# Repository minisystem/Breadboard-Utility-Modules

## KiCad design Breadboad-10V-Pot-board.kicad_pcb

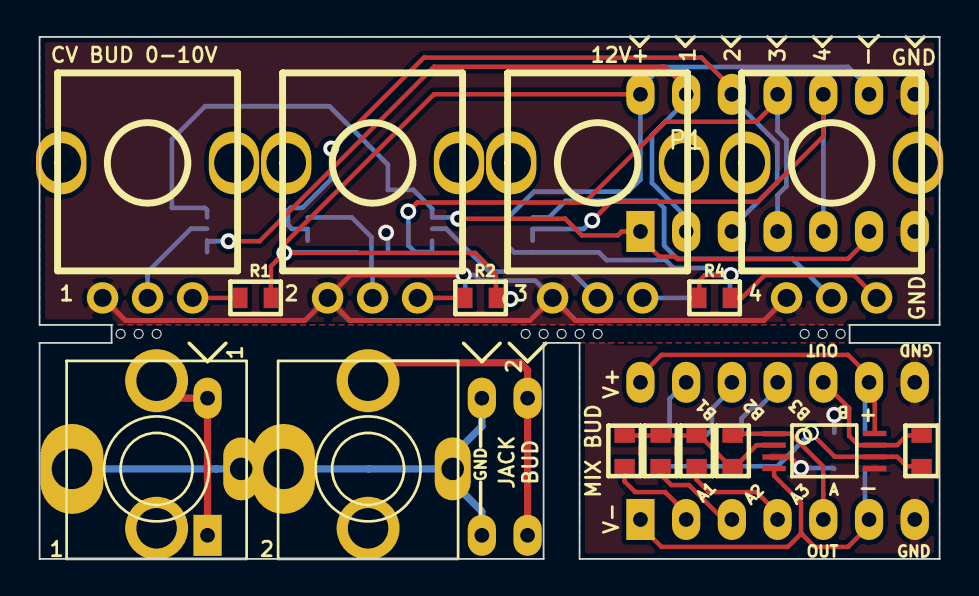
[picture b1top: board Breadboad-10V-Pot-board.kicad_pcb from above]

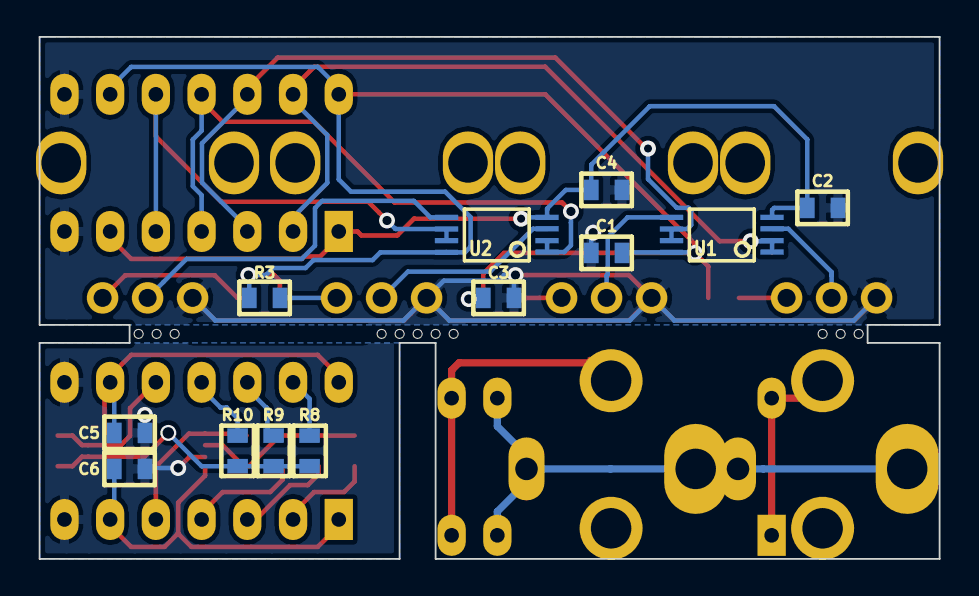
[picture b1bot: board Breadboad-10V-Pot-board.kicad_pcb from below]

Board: 2 copper layers, 50.0 x 29.0 mm, 44 parts (12 on the bottom side), 27 nets.

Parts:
C1, C2, C3, C4, C5, C6: C_US; SM0603-C-JRL
HOLE-0.125-INCH, HOLE-0.125-INCH#2, HOLE-0.125-INCH#3, HOLE-0.125-INCH#4, HOLE-0.125-INCH#5, HOLE-0.125-INCH#6, HOLE-0.125-INCH#7, HOLE-0.125-INCH#8, HOLE-0.125-INCH#9, HOLE-0.125-INCH#10, HOLE-0.125-INCH#11, HOLE-0.125-INCH#12, HOLE-0.125-INCH#13: VAL**; HOLE-0.125-INCH
J1, J2: JACK_MONO_SW; PJ-301B-JACK
P1, P2: DIP14; DIP-14__300_ELL
P3, P3#2: DIP_6; DIP-6__300_ELL
R1, R2, R3, R4: 10K; SM0603-R-JRL
R5, R6, R7, R8, R9, R10, R11, R12: 100K; SM0603-R-JRL
U1, U2, U3: TL072-; TSSOP8-JRL
VR1, VR2, VR3, VR4: 50K; RD901F-ALPHA-POT

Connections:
+12V: C1.1, C3.1, C5.1, P1.9, P1.14, P2.9, P2.14, R1.1, R2.1, R3.1, R4.1, U1.8, U2.8, U3.8
-12V: C2.2, C4.2, C6.2, P1.1, P1.6, P2.1, P2.6, U1.4, U2.4, U3.4
CV1: P1.2, P1.13, U1.1, U1.2
CV2: P1.3, P1.12, U1.6, U1.7
CV3: P1.4, P1.11, U2.1, U2.2
CV4: P1.5, P1.10, U2.6, U2.7
GND: C1.2, C2.1, C3.2, C4.1, C5.2, C6.1, J1.1, J2.1, P1.7, P1.8, P2.7, P2.8, P3#2.2, P3#2.5, U3.3, U3.5, VR1.1, VR2.1, VR3.1, VR4.1
JACK1: J1.3, P3.1, P3.6
JACK2: J2.3, P3#2.3, P3#2.4
MIXA-IN1: P2.2, R5.2
MIXA-IN2: P2.3, R6.2
MIXA-IN3: P2.4, R7.2
MIXA-OUT: P2.5, R11.1, U3.1
MIXB-IN1: P2.13, R8.2
MIXB-IN2: P2.12, R9.2
MIXB-IN3: P2.11, R10.2
MIXB-OUT: P2.10, R12.1, U3.7
unnamed: R1.2, VR1.3
unnamed: R2.2, VR2.3
unnamed: R3.2, VR3.3
unnamed: R4.2, VR4.3
unnamed: R8.1, R9.1, R10.1, R12.2, U3.6
unnamed: R5.1, R6.1, R7.1, R11.2, U3.2
unnamed: U1.3, VR1.2
unnamed: U1.5, VR2.2
unnamed: U2.3, VR3.2
unnamed: U2.5, VR4.2

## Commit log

2015-04-11 added jack board and laid out mechanical holes for panel separation
2015-04-11 cleaning up silkscreen
2015-04-12 silkscreen adjusted, ready to order. May have problem with NPTH holes with DirtyPCBs
2015-04-26 sent for fabrication
